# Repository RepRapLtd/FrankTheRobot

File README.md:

This is a small robot for testing out LIDAR scanning rangefinders, automatic environment mapping, 21st century Grey-Walter tortoise like behaviour etc.

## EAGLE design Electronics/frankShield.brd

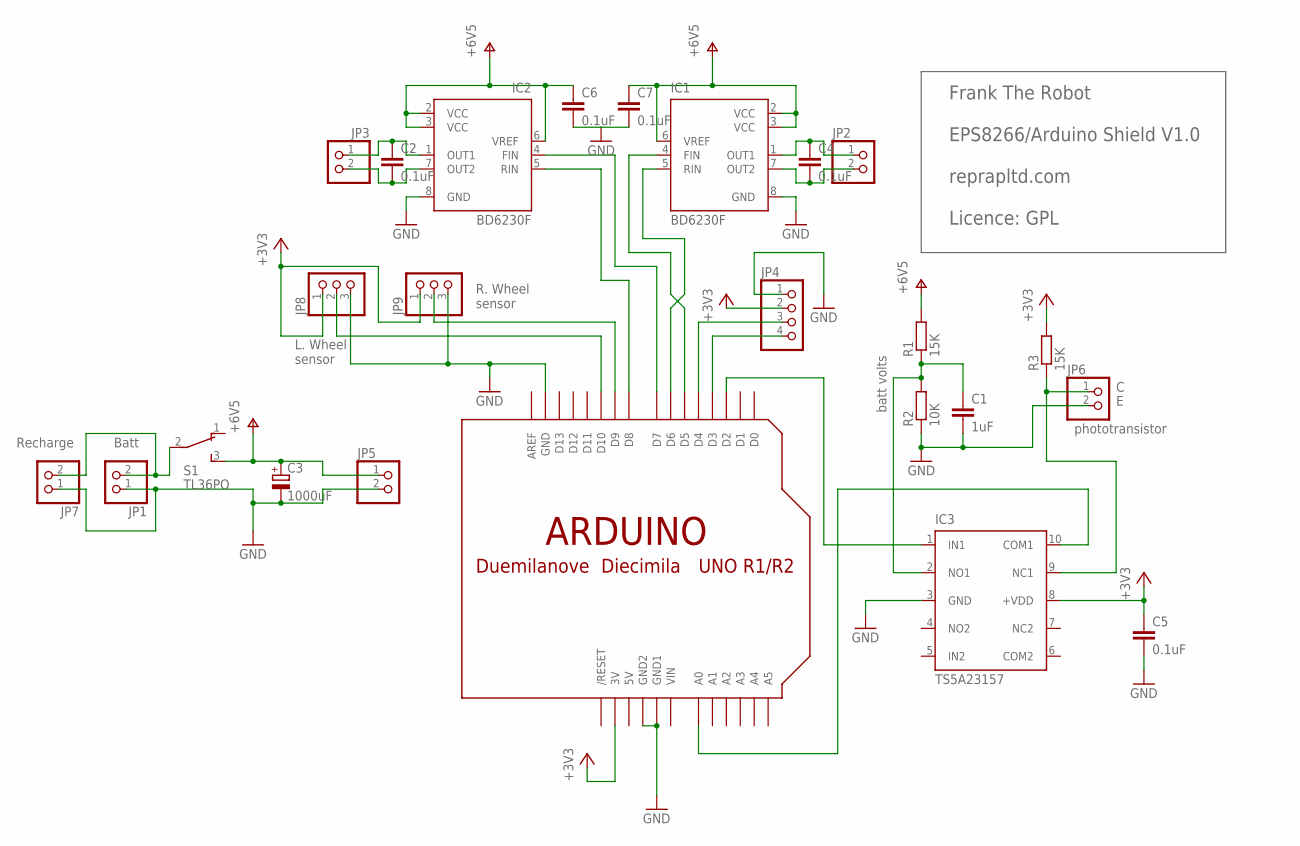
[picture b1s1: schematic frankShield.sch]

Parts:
C1: 1uF; C0805
C2, C4, C5, C6, C7: 0.1uF; C0805
C3: 1000uF; B45181B
IC1, IC2: BD6230F; SOP8
IC3: TS5A23157; MSOP10
JP1, JP2, JP3, JP5, JP6, JP7: PINHD-1X2; 1X02
JP4: PINHD-1X4; 1X04
JP8, JP9: PINHD-1X3; 1X03
R1, R3: 15K; M0805
R2: 10K; M0805
S1: TL36PO; TL3XPO
U$1: ARDUINO-BPLACE

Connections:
5V: U$1.5V
+3V3: C5.1, IC3.8 (+VDD), JP4.2, JP8.1, JP9.1, R3.2, U$1.3V
GND: C1.2, C3.-, C5.2, C6.2, C7.2, IC1.8 (GND), IC2.8 (GND), IC3.3 (GND), JP1.1, JP4.1, JP5.2, JP6.2, JP7.1, JP8.3, JP9.3, R2.1, U$1.GND, U$1.GND1, U$1.GND2
unnamed: JP4.4, U$1.D3
unnamed: JP4.3, U$1.D4
unnamed: C2.1, IC2.1 (OUT1), JP3.1
unnamed: C2.2, IC2.7 (OUT2), JP3.2
unnamed: C4.1, IC1.1 (OUT1), JP2.1
unnamed: C4.2, IC1.7 (OUT2), JP2.2
unnamed: IC1.5 (RIN), U$1.D6
unnamed: IC1.4 (FIN), U$1.D5
unnamed: IC2.4 (FIN), U$1.D7
unnamed: IC2.5 (RIN), U$1.D8
unnamed: IC3.10 (COM1), U$1.A0
unnamed: C1.1, IC3.2 (NO1), R1.1, R2.2
unnamed: JP1.2, JP7.2, S1.2
unnamed: IC3.9 (NC1), JP6.1, R3.1
unnamed: IC3.1 (IN1), U$1.D2
unnamed: JP9.2, U$1.D9
unnamed: JP8.2, U$1.D10
NC2: IC3.7 (NC2)
V+: C3.+, C6.1, C7.1, IC1.2 (VCC), IC1.3 (VCC), IC1.6 (VREF), IC2.2 (VCC), IC2.3 (VCC), IC2.6 (VREF), JP5.1, R1.2, S1.3 (S)
VIN: U$1.VIN

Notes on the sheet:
phototransistor
Frank The Robot EPS8266/Arduino Shield V1.0 reprapltd.com Licence: GPL
Batt
Recharge
L. Wheel sensor
R. Wheel sensor
batt volts

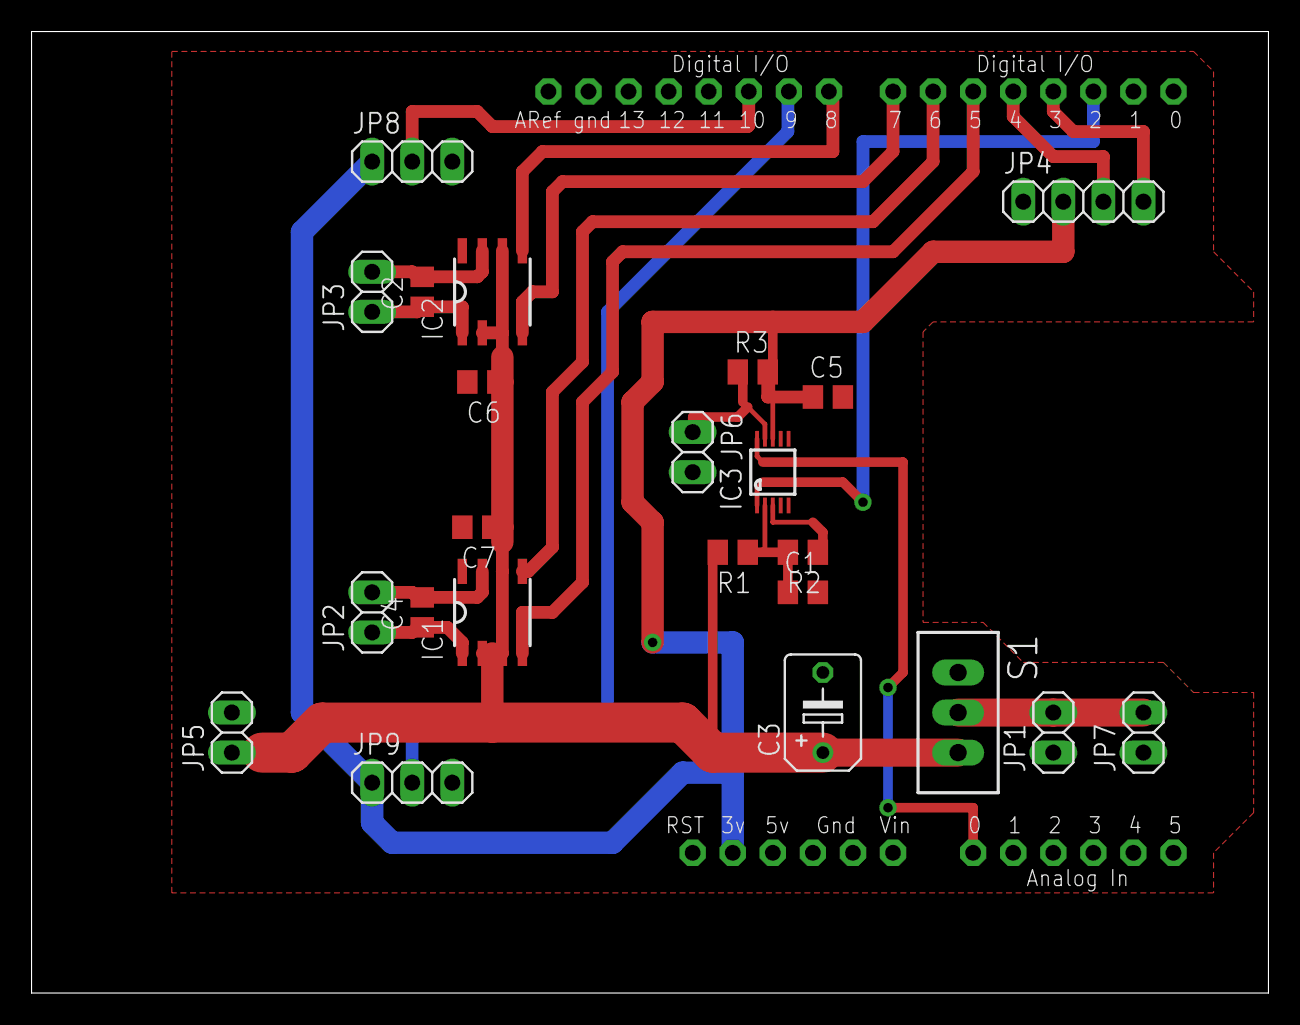
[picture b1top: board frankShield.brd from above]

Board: 2 copper layers, 78.4 x 61.0 mm, 24 parts (0 on the bottom side), 20 nets.

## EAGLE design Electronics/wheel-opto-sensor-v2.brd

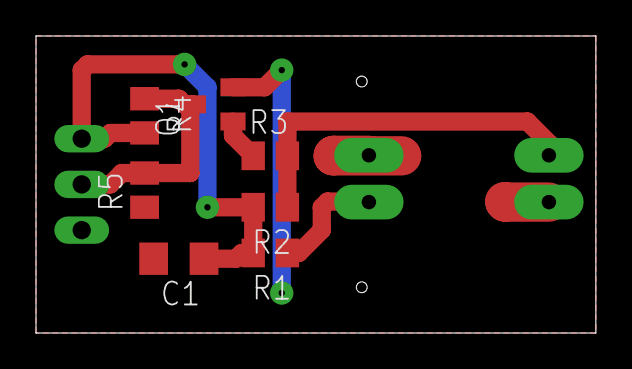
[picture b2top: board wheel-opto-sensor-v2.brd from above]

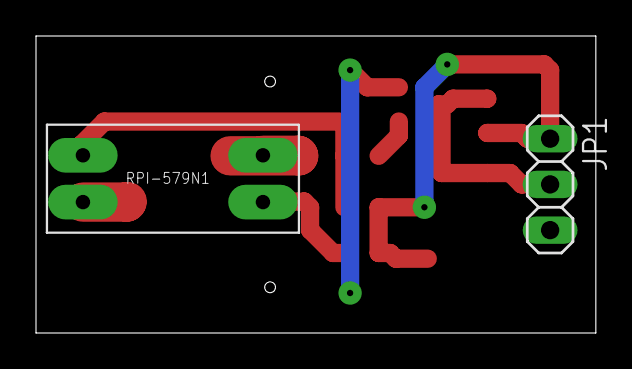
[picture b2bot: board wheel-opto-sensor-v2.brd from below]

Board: 2 copper layers, 31.1 x 16.5 mm, 9 parts (2 on the bottom side), 6 nets.

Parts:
C1: 10uF; C1206
JP1: 1X03
Q1: SOT23
R1: 120R; M0805
R2: 1K8; M0805
R3: 10K; M0805
R4: 1K2; M0805
R5: 1K; M0805
U$1: RPI-579N1

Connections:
+3V3: C1.1, JP1.1, R1.2, R2.2, R4.2
GND: C1.2, JP1.3, Q1.2, R5.1, U$1.P$2, U$1.P$4
unnamed: JP1.2, Q1.3, R4.1, R5.2
unnamed: R1.1, U$1.P$1
unnamed: Q1.1, R3.1
unnamed: R2.1, R3.2, U$1.P$3

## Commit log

2017-12-18 New software that behaves sensibly with obstacles.
2017-12-19 1st hack at the shield design for WiFi Frank...
2017-12-21 Improved shield design. GERBER files added.
2017-12-21 Just testing the clean function...
2018-01-04 Added opposite rotation on bump and additional "wiggle" scan every 10 secs
2018-01-08 Added Frank's picture...
    Also Sally w.i.p. on the WiFi version.
2018-01-31 Updated electronics to power the wheel sensors directly off the battery. (They take too much current from 3V3 if that is used; the sensors now have potential dividers so their output never exceeds 3v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
    Added a PCB test program for the Wemos D1/ESP8266 board (W.I.P.)
2018-02-01 Increased diameter of optosensor vias to make them easier to mill.
2018-02-01 Added LED to shield, and anti-short safety diode to the charge circuit.
2018-05-11 PCBs corrected (D9 now LED) and improved (wheel sensor has 4 mounting holes); software updated to match.
2018-06-08 PCB test program updated; all works.
    TODO: write motor callibration function
    update schematic and PCB to take account of the use of the
    LED pin for input
2018-06-11 Caution update...
2018-06-20 Wemos MINI PCB added. Corrections to battery holder W.I.P.
2018-06-24 Sally's design mods.
2019-01-25 Added phototransistor 665-5347 to schematic.
2019-01-30 File tidying.
2019-05-20 Latest control prog (0.3) W.I.P.
2019-05-22 Compiles without errors...
2020-05-19 Starting work on Frank 2.0.
    Shaft opto encoder and motor/voltage speed experiment.
2020-05-20 Electronics for Frank 2.0 WIP.
2020-05-21 Frank 2 electronics WIP.
2020-05-22 Frank 2.0 electronics WIP.
2020-05-22 Now with indicator LEDs...
2020-05-25 Electronics WIP
2020-05-26 PCB WIP
2020-05-27 PCB finished (but probably not final...) Except for silks
2020-07-03 Updating lots of Frank 2.0 stuff...
2020-07-30 Improved motor mount and sensor. Improved motor test program.
2020-07-31 Improved motor test program WIP.
2020-08-03 Improved motor test program now working.
2020-08-12 Motor and castor design improvements. I2C pullup resistors added.
2020-09-02 Updated s/w and PCB
2021-03-25 PCB as prototyped.
2024-05-29 Updating
